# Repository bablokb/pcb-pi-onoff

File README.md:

pcb-pi-onoff
============

Overview
--------

This project contains the KiCAD-project-files for a small
power-control pHat. A PIC-MCU controls the power for the Pi. On/off is
via a push-button or an IR-remote. Before cutting current, the PIC
sends a shutdown request to the Pi. Once done, the Pi signals
shutdown-complete to the PIC which in turn cuts power.

Status
------

**this is work-in-progress!**

  - production: OK
  - basic firmware: tested
  - basic functional test: open
  - test with RTC: open
  - IR firmware: open
  - IR test: open

PCB
---

The KiCAD-sources for the pHat are in the sub-directory
[pcb-pi-onoff](pcb-pi-onoff), production-files with
gerber-layers, drill-hole files, bom and pick-and-place-file are in
the sub-directory [production](production). Note that the pcb and the
bom/cpl-files are optimzied for JLCPCB. Please check with your
pcb-factory if these files meet their requirements.

Schematic
---------

Layout
------

3D-View
-------

Configuration
-------------

Please read the description of the [firmware](pic-firmware/README.md) for
how to configure the Pi and the PIC.

License
-------

[![CC BY-SA 4.0][cc-by-sa-shield]][cc-by-sa]

This work is licensed under a
[Creative Commons Attribution-ShareAlike 4.0 International
License][cc-by-sa].

[![CC BY-SA 4.0][cc-by-sa-image]][cc-by-sa]

[cc-by-sa]: http://creativecommons.org/licenses/by-sa/4.0/
[cc-by-sa-image]: https://licensebuttons.net/l/by-sa/4.0/88x31.png
[cc-by-sa-shield]:
https://img.shields.io/badge/License-CC%20BY--SA%204.0-lightgrey.svg

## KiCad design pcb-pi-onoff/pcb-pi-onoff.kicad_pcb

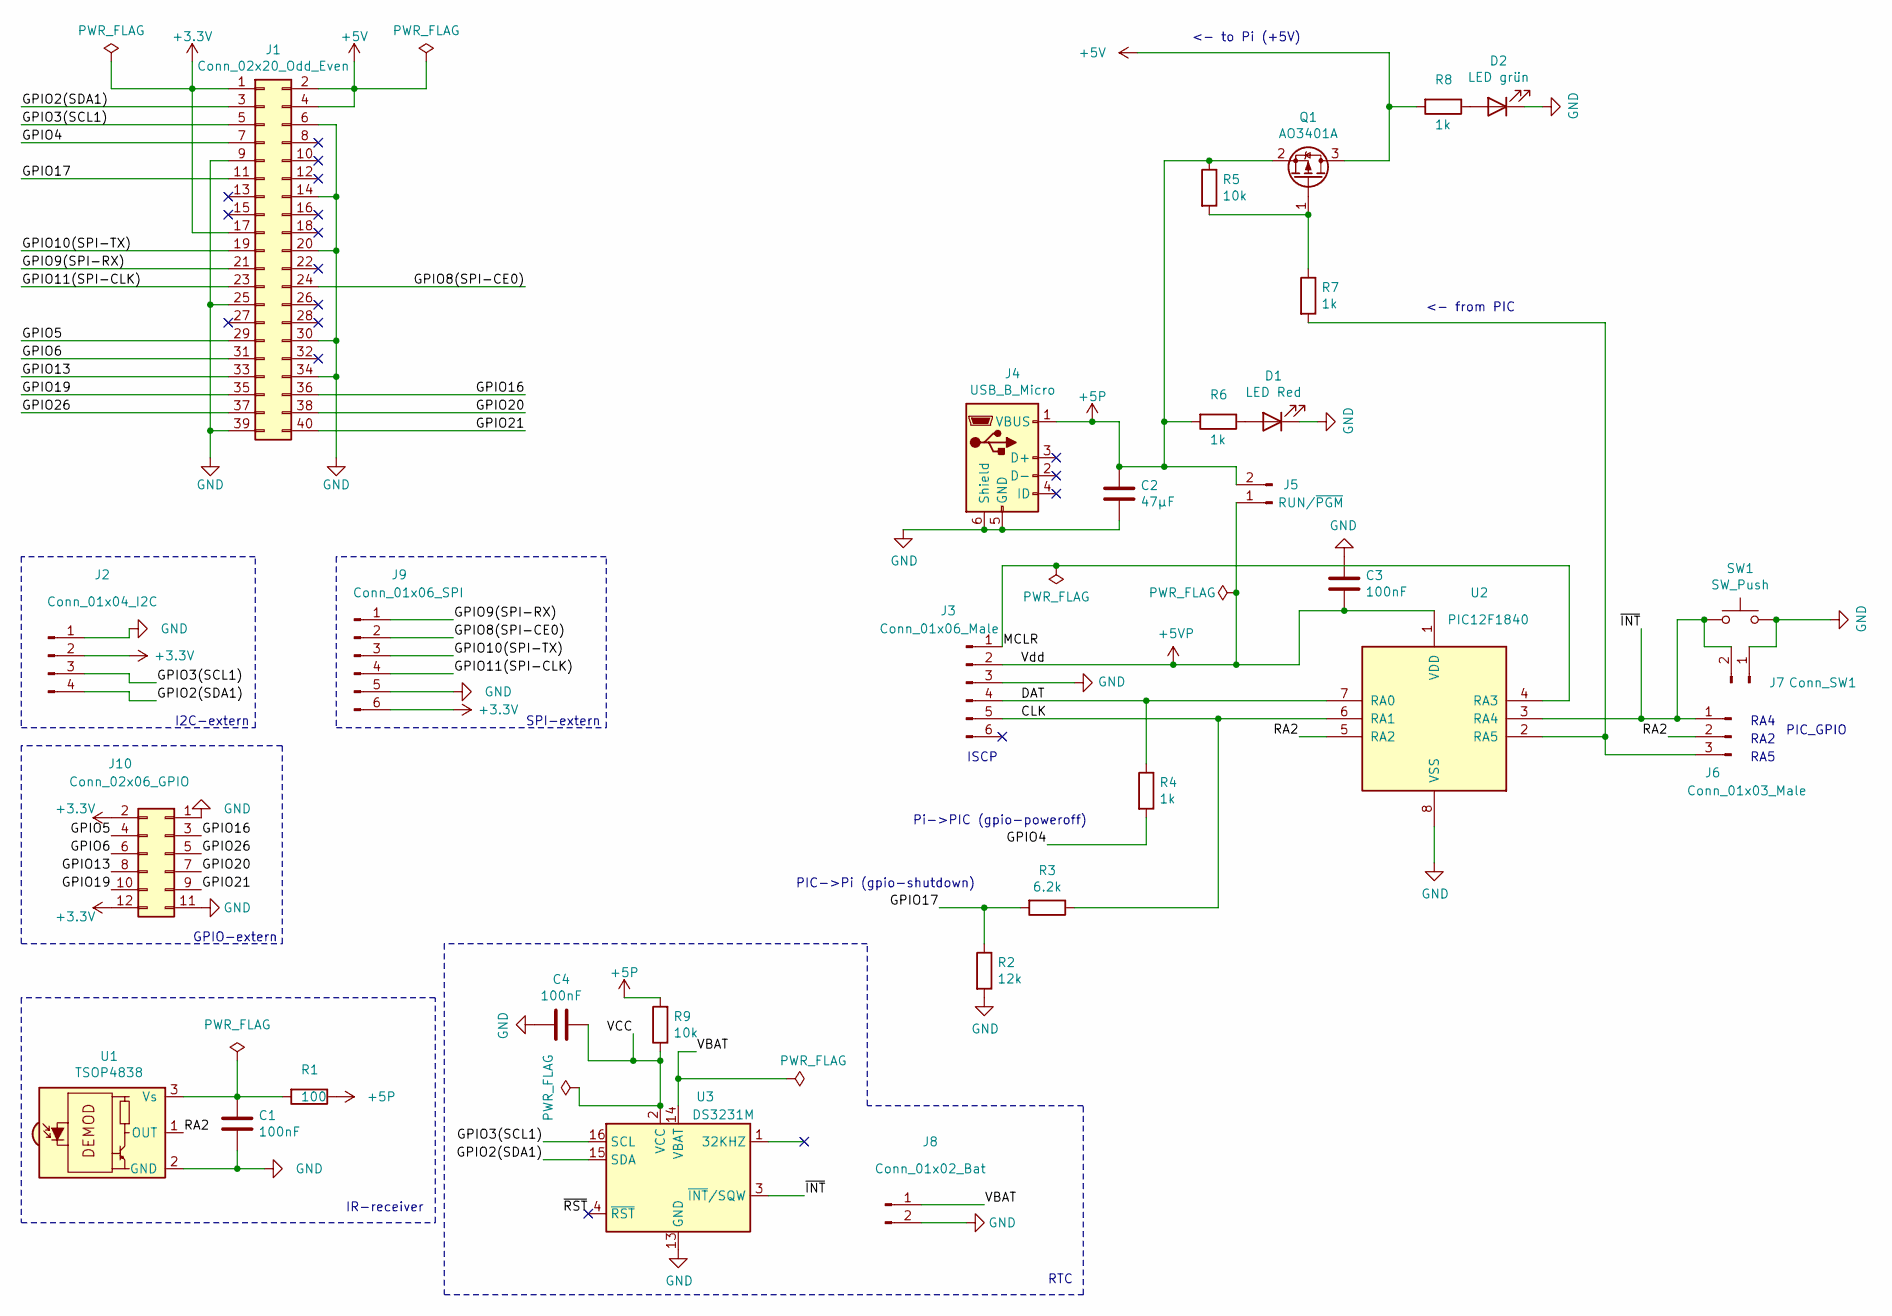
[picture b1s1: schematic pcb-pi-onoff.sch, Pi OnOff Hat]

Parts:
C1, C3, C4: 100nF; C_0805_2012Metric; LCSC C24497
C2: 47µF; C_1206_3216Metric; LCSC C96123
D1: LED Red; LED_0805_2012Metric; LCSC C84256
D2: LED grün; LED_0805_2012Metric; LCSC C2297
J1: Conn_02x20_Odd_Even; PinSocket_2x20_P2.54mm_Vertical
J2: Conn_01x04_I2C; PinHeader_1x04_P2.54mm_Vertical
J3: Conn_01x06_Male; PinHeader_1x06_P2.54mm_Vertical
J4: USB_B_Micro; USB_Micro-B_JLCPCB_40942; LCSC C40942
J5: RUN/~PGM~; PinHeader_1x02_P2.54mm_Vertical
J6: Conn_01x03_Male; PinHeader_1x03_P2.54mm_Vertical
J7: Conn_SW1; PinHeader_1x02_P2.54mm_Vertical
J8: Conn_01x02_Bat; PinHeader_1x02_P2.54mm_Vertical
J9: Conn_01x06_SPI; PinHeader_1x06_P2.54mm_Vertical
J10: Conn_02x06_GPIO; PinHeader_2x06_P2.54mm_Vertical
Q1: AO3401A; SOT-23; LCSC C15127
R1: 100; R_0805_2012Metric; LCSC C17408
R2: 12k; R_0805_2012Metric; LCSC C17444
R3: 6.2k; R_0805_2012Metric; LCSC C17767
R4, R6, R7, R8: 1k; R_0805_2012Metric; LCSC C17513
R5, R9: 10k; R_0805_2012Metric; LCSC C17414
SW1: SW_Push; SW_PUSH_SLIM_1x4
U1: TSOP4838; Vishay_MOLD-3Pin
U2: PIC12F1840; SO-8_3.9x4.9mm_P1.27mm_HandSolder
U3: DS3231M; SOIC-16W_7.5x10.3mm_P1.27mm_HandSolder

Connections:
+3V3: J1.1, J1.17, J2.2, J9.6, J10.2, J10.12
+5P: C2.1, J4.1 (VBUS), J5.2, Q1.2 (S), R1.1, R5.1, R6.2, R9.2
+5V: J1.2, J1.4, Q1.3 (D), R8.2
+5VP: C3.2, J3.2, J5.1, U2.1 (VDD)
/CLK: J3.5, R3.1, U2.6 (RA1)
/DAT: J3.4, R4.1, U2.7 (RA0)
/GPIO2(SDA1): J1.3, J2.4, U3.15 (SDA)
/GPIO3(SCL1): J1.5, J2.3, U3.16 (SCL)
/GPIO4: J1.7, R4.2
/GPIO5: J1.29, J10.4
/GPIO6: J1.31, J10.6
/GPIO8(SPI-CE0): J1.24, J9.2
/GPIO9(SPI-RX): J1.21, J9.1
/GPIO10(SPI-TX): J1.19, J9.3
/GPIO11(SPI-CLK): J1.23, J9.4
/GPIO13: J1.33, J10.8
/GPIO16: J1.36, J10.3
/GPIO17: J1.11, R2.1, R3.2
/GPIO19: J1.35, J10.10
/GPIO20: J1.38, J10.7
/GPIO21: J1.40, J10.9
/GPIO26: J1.37, J10.5
/MCLR: J3.1, U2.4 (RA3)
/RA2: J6.2, U1.1 (OUT), U2.5 (RA2)
/VBAT: J8.1, U3.14 (VBAT)
/VCC: C4.1, R9.1, U3.2 (VCC)
/~INT: J6.1, J7.2, SW1.1, U2.3 (RA4), U3.3 (~INT~/SQW)
/~RST: U3.4 (~RST)
GND: C1.2, C2.2, C3.1, C4.2, D1.1 (K), D2.1 (K), J1.6, J1.9, J1.14, J1.20, J1.25, J1.30, J1.34, J1.39, J2.1, J3.3, J4.5 (GND), J4.6 (Shield), J7.1, J8.2, J9.5, J10.1, J10.11, R2.2, SW1.2, U1.2 (GND), U2.8 (VSS), U3.5 (GND), U3.6 (GND), U3.7 (GND), U3.8 (GND), U3.9 (GND), U3.10 (GND), U3.11 (GND), U3.12 (GND), U3.13 (GND)
unnamed: C1.1, R1.2, U1.3 (Vs)
unnamed: D1.2 (A), R6.1
unnamed: D2.2 (A), R8.1
unnamed: J6.3, R7.2, U2.2 (RA5)
unnamed: Q1.1 (G), R5.2, R7.1

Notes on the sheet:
PIC_GPIO
ISCP
Pi->PIC (gpio-poweroff)
PIC->Pi (gpio-shutdown)
RA4
RA2
<- from PIC
<- to Pi (+5V)
RA5
I2C-extern
SPI-extern
GPIO-extern
IR-receiver
RTC

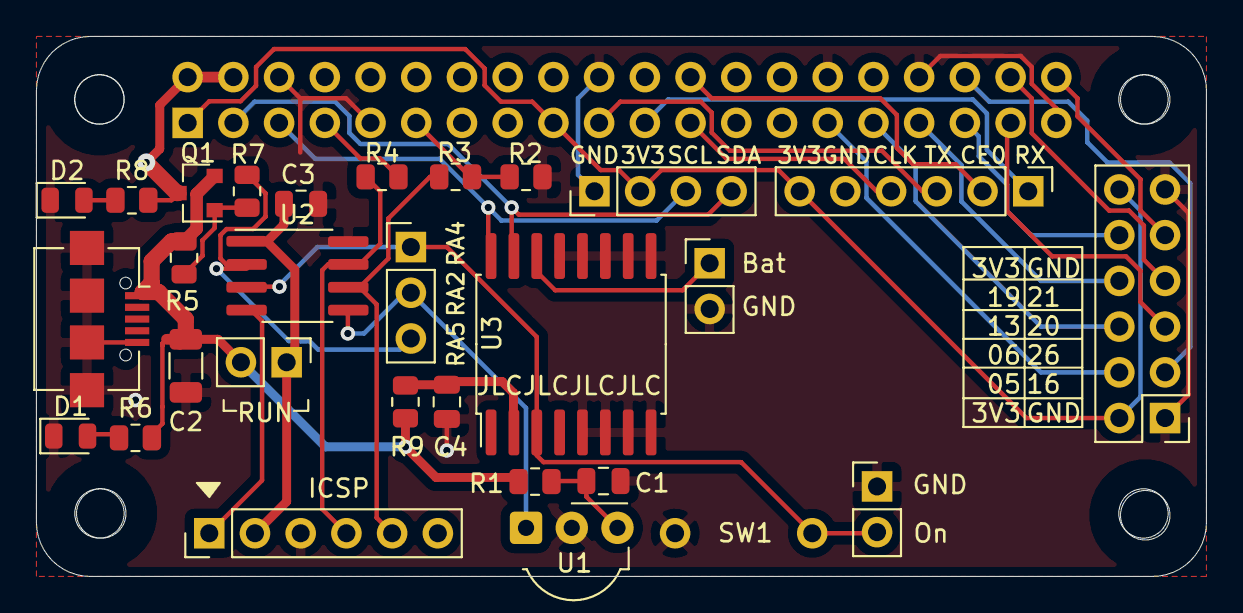
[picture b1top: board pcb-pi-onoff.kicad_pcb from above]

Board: 2 copper layers, 65.0 x 30.0 mm, 30 parts (1 on the bottom side), 33 nets.

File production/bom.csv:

Comment,Designator,Footprint,LCSC
"47µF","C2","Capacitor_SMD:C_1206_3216Metric","C96123"
"100nF","C1,C3,C4","Capacitor_SMD:C_0805_2012Metric","C24497"
"LED Red","D1","LED_SMD:LED_0805_2012Metric","C84256"
"LED grün","D2","LED_SMD:LED_0805_2012Metric","C2297"
"Conn_02x20_Odd_Even","J1","Connector_PinSocket_2.54mm:PinSocket_2x20_P2.54mm_Vertical",""
"Conn_02x06_GPIO","J10","Connector_PinHeader_2.54mm:PinHeader_2x06_P2.54mm_Vertical",""
"Conn_01x04_I2C","J2","Connector_PinHeader_2.54mm:PinHeader_1x04_P2.54mm_Vertical",""
"Conn_01x06_Male","J3","Connector_PinHeader_2.54mm:PinHeader_1x06_P2.54mm_Vertical",""
"USB_B_Micro","J4","user:USB_Micro-B_JLCPCB_40942","C40942"
"RUN/~PGM~","J5","Connector_PinHeader_2.54mm:PinHeader_1x02_P2.54mm_Vertical",""
"Conn_01x03_Male","J6","Connector_PinHeader_2.54mm:PinHeader_1x03_P2.54mm_Vertical",""
"Conn_SW1","J7","Connector_PinHeader_2.54mm:PinHeader_1x02_P2.54mm_Vertical",""
"Conn_01x02_Bat","J8","Connector_PinHeader_2.54mm:PinHeader_1x02_P2.54mm_Vertical",""
"Conn_01x06_SPI","J9","Connector_PinHeader_2.54mm:PinHeader_1x06_P2.54mm_Vertical",""
"AO3401A","Q1","Package_TO_SOT_SMD:SOT-23","C15127"
"100","R1","Resistor_SMD:R_0805_2012Metric","C17408"
"12k","R2","Resistor_SMD:R_0805_2012Metric","C17444"
"6.2k","R3","Resistor_SMD:R_0805_2012Metric","C17767"
"10k","R5,R9","Resistor_SMD:R_0805_2012Metric","C17414"
"1k","R4,R6,R7,R8","Resistor_SMD:R_0805_2012Metric","C17513"
"SW_Push","SW1","user:SW_PUSH_SLIM_1x4",""
"TSOP4838","U1","OptoDevice:Vishay_MOLD-3Pin",""
"PIC12F1840","U2","Package_SO:SO-8_3.9x4.9mm_P1.27mm",""
"DS3231M","U3","Package_SO:SOIC-16W_7.5x10.3mm_P1.27mm",""

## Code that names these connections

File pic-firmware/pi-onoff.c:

// --------------------------------------------------------------------------
// Firmware for power-control pHat
//
// This project uses the following pins:
//  - PIN_FROM_PI (RA0): Pi confirms shutdown (PIC can turn off power)
//  - PIN_TO_PI   (RA1): request shutdown from Pi
//  - PIN_IR      (RA2): infrared signal (not implemented)
//  - PIN_SIG     (RA4): external on/off signal (RTC and button)
//  - PIN_POWER   (RA5): attach to gate of mosfet to turn power on or off
//
// Author: Bernhard Bablok
//
// https://github.com/bablokb/pcb-pi-onoff
// 
// --------------------------------------------------------------------------

#include "picconfig.h"
#include <stdint.h>

#include "delay.h"

#ifndef PIN_FROM_PI
  #define PIN_FROM_PI 0
#endif
#define GP_FROM_PI _CONCAT(RA,PIN_FROM_PI)

#ifndef PIN_TO_PI
  #define PIN_TO_PI 1
#endif
#define GP_TO_PI _CONCAT(RA,PIN_TO_PI)

#ifndef PIN_IR
  #define PIN_IR 2
#endif
#define GP_IR _CONCAT(RA,PIN_IR)

#ifndef PIN_SIG
  #define PIN_SIG 4
#endif
#define GP_SIG _CONCAT(RA,PIN_SIG)

#ifndef PIN_POWER
  #define PIN_POWER 5
#endif
#define GP_POWER _CONCAT(RA,PIN_POWER)

#define BOOT_WAIT   20               // 5s = 20*250ms
#define POWER_ON    0
#define POWER_OFF   1

CONFIG_WORDS;

static uint8_t is_booting = 0;

////////////////////////////////////////////////////////////////////////
// Intialize registers

static void init(void) {
  // configure registers
  __asm__ ("CLRWDT");             // clear WDT even if WDT is disabled
  TRISA     = 0b010101;           // GP4, GP2, GP0 are input
  ANSELA    = 0;                  // no analog input
  CM1CON0   = 0x07;               // disable comparator for GP0-GP2
  WPUA      = 0b010100;           // weak pullups enable on GP2, GP4
  NOT_GPPU  = 0;                  // enable pullups
  IOCAN     = 0b010101;           // IOC for all input pins

  PORTA    = 0;                   // initial value of GPIOs
  GP_POWER = POWER_OFF;           //    except GP_POWER
  GP_TO_PI = 1;                   //    except GP_TO_PI

  INTCON   = 0;                   // clear interrupt flag bits
  IOCIE    = 1;                   // enable IOC
  GIE      = 1;                   // global interrupt enable
}

// --- interrupt service routine   ------------------------------------------

static void isr(void) __interrupt 0 {
  if (IOCIF) {                           // interrupt-on-change
    if (!GP_SIG) {                       // PIN_SIG low
      if (GP_POWER == POWER_OFF) {       // power is off:
        GP_POWER = POWER_ON;             //   turn power on and
        is_booting = 1;                  //   configure wait
      } else {                           // power is on:
        GP_TO_PI = 0;                    //   signal shutdown to Pi
      }
      delay_ms(50);                      // debounce GP_SIG

    } else if (GP_FROM_PI) {             // High: shutdown complete
      GP_POWER = POWER_OFF;              // turn power off
      GP_TO_PI = 1;                      // and restore initial state
      is_booting = 0;                    // (should not be necessary)
    }
    IOCIF = 0;                           // clear IOC interrupt flag
  }
}

// --- main program   -------------------------------------------------------

// - calibrate internal clock
// - initialize registers
// - loop forever (sleep not possible because IOC can't wake device)

void main(void) {
  INIT_SPECIAL;
  init();
  while (1) {
    if (is_booting) {
      GIE = 0;                               // disable interrupts
      for (uint8_t i=0; i<BOOT_WAIT; ++i) {
        delay_ms(250);
      }
      is_booting = 0;
      GIE = 1;                               // global interrupt enable
    }
  }
}

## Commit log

2021-06-08 added url/revision on B.SilkS
2021-06-08 added I2C-connector
2021-06-08 added SPI-connector
2021-06-08 added GPIO-connector
2021-06-08 replaced footprints for PIC and RTC with handsolder-version
2021-06-09 Rev 1.0: changed 3V3/GND on GPIO-connector
2021-06-09 added basic content
2021-10-30 added section about license
2021-11-05 added xc8 intermediate files
2021-11-05 add more status info, reorder text
